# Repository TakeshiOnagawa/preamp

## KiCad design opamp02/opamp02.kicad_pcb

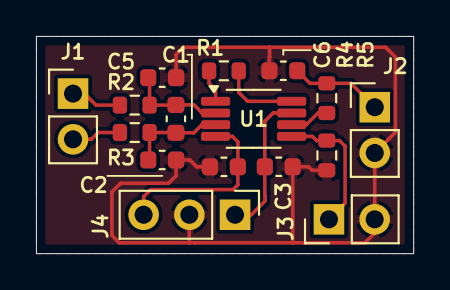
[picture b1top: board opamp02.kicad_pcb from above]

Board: 2 copper layers, 21.0 x 12.1 mm, 16 parts (0 on the bottom side), 12 nets.

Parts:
C1, C2, C5: 22pF; C_0603_1608Metric
C3, C4: 0.1uF; C_0603_1608Metric
C6: 22p; C_0603_1608Metric
J1, J2, J3: Conn_01x02; PinHeader_1x02_P2.54mm_Vertical
J4: Conn_01x03; PinHeader_1x03_P2.54mm_Vertical
R1: 499R; R_0603_1608Metric
R2, R3, R4: 10k; R_0603_1608Metric
R5: 0.1; R_0603_1608Metric
U1: INA823DGK; VSSOP-8_3x3mm_P0.65mm

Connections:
0: C2.2, C3.2, C4.2, C5.1, C6.2, J2.2, J3.2, J4.2, R5.1
+5VA: C3.1, J4.1, U1.7 (Vs+)
-5VA: C4.1, J4.3, U1.4 (Vs-)
IN+: J1.2, R3.1
IN-: J1.1, R2.1
unnamed: R1.1, U1.1 (Rg)
unnamed: R1.2, U1.8 (Rg)
unnamed: C1.2, C2.1, R3.2, U1.3 (+)
unnamed: C1.1, C5.2, R2.2, U1.2 (-)
unnamed: R4.1, U1.6 (OUT)
OUT: C6.1, J2.1, R4.2
REF: J3.1, R5.2, U1.5 (Ref)
